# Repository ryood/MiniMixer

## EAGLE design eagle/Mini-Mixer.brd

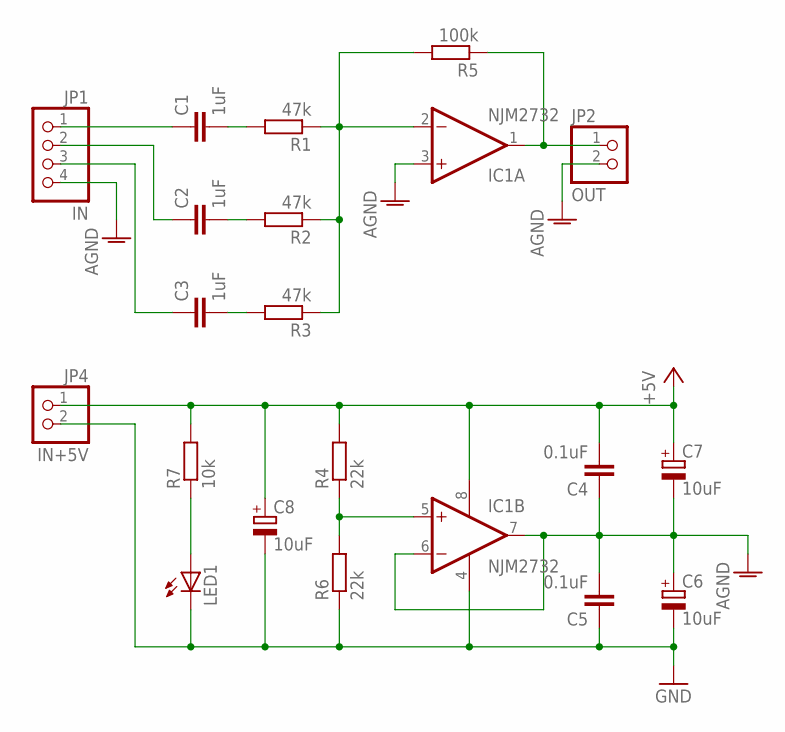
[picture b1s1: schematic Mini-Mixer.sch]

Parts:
C1, C2, C3: 1uF; C050-050X075
C4, C5: 0.1uF; C025-024X044
C6, C7, C8: 10uF; TT2D4L
IC1: NJM2732; DIL08
JP1: IN; 1X04
JP2: OUT; 1X02
JP4: IN+5V; 1X02
LED1: LED3MM
R1, R2, R3: 47k; 0207/7
R4, R6: 22k; 0207/7
R5: 100k; 0207/7
R7: 10k; 0207/7

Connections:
+5V: C4.2, C7.+, C8.+, IC1.8 (V+), JP4.1, R4.2, R7.2
AGND: C4.1, C5.2, C6.+, C7.-, IC1.3 (+IN), IC1.6 (-IN), IC1.7 (OUT), JP1.4, JP2.2
GND: C5.1, C6.-, C8.-, IC1.4 (V-), JP4.2, LED1.K (C), R6.1
unnamed: C1.1, JP1.1
unnamed: C2.1, JP1.2
unnamed: C3.1, JP1.3
unnamed: C1.2, R1.2
unnamed: C2.2, R2.2
unnamed: C3.2, R3.2
unnamed: IC1.2 (-IN), R1.1, R2.1, R3.1, R5.2
unnamed: LED1.A, R7.1
unnamed: IC1.1 (OUT), JP2.1, R5.1
unnamed: IC1.5 (+IN), R4.1, R6.2

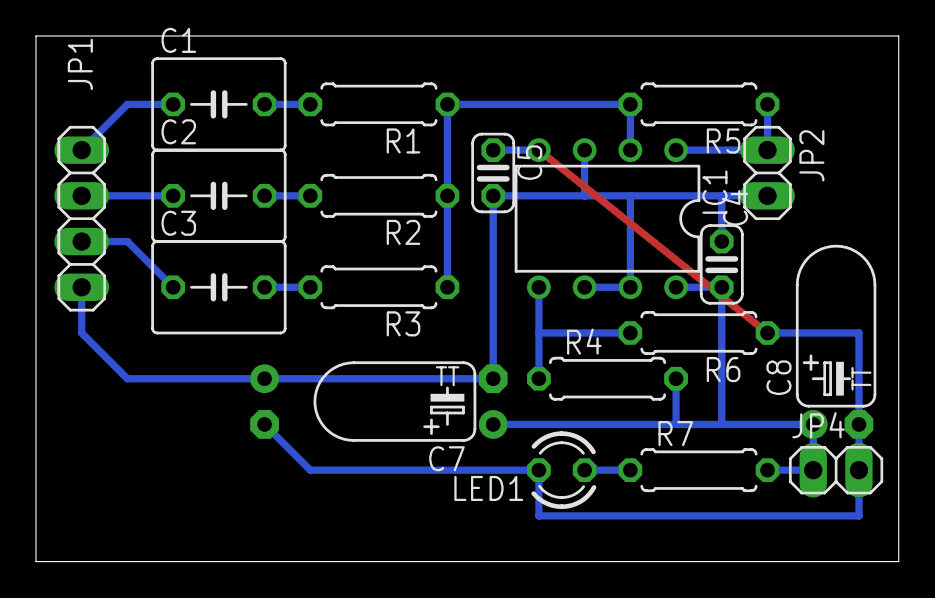
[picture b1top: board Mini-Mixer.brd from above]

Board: 2 copper layers, 47.9 x 29.2 mm, 20 parts (1 on the bottom side), 13 nets.

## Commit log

2015-06-25 Board Design Fix
2015-06-30 case内配線図追加
